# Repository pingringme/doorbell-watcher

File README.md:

# PingRing.me - Smart Doorbell

## 🌟 About PingRing.me

PingRing.me modernizes your existing doorbell by adding notifications via SMS, WhatsApp, HTTP, MQTT, and more. This enhancement ensures you never miss a visitor, whether you're outside or wearing noise-canceling headphones. The system integrates seamlessly with your current doorbell setup, allowing you to track arrivals and receive timely notifications.

## 🛠️ Features

- **Multi-Channel Notifications:** Receive alerts through SMS, WhatsApp, HTTP, MQTT, etc.
- **Seamless Integration:** Compatible with existing doorbell systems.
- **Local Web Server:** Access device information and perform over-the-air updates.
- **Open Source:** Hardware designs and code are publicly available.

## 📸 Visuals

Check [website here https://pingring.me](https://pingring.me)

## 🛠️ Tech Stack

- **Microcontroller:** ESP32-PICO-D4
- **Programming Language:** C (Arduino)
- **Cloud Functions:** AWS Lambda (Python)
- **Hardware Platform:** [TinyPICO USB-C](https://www.tinypico.com)

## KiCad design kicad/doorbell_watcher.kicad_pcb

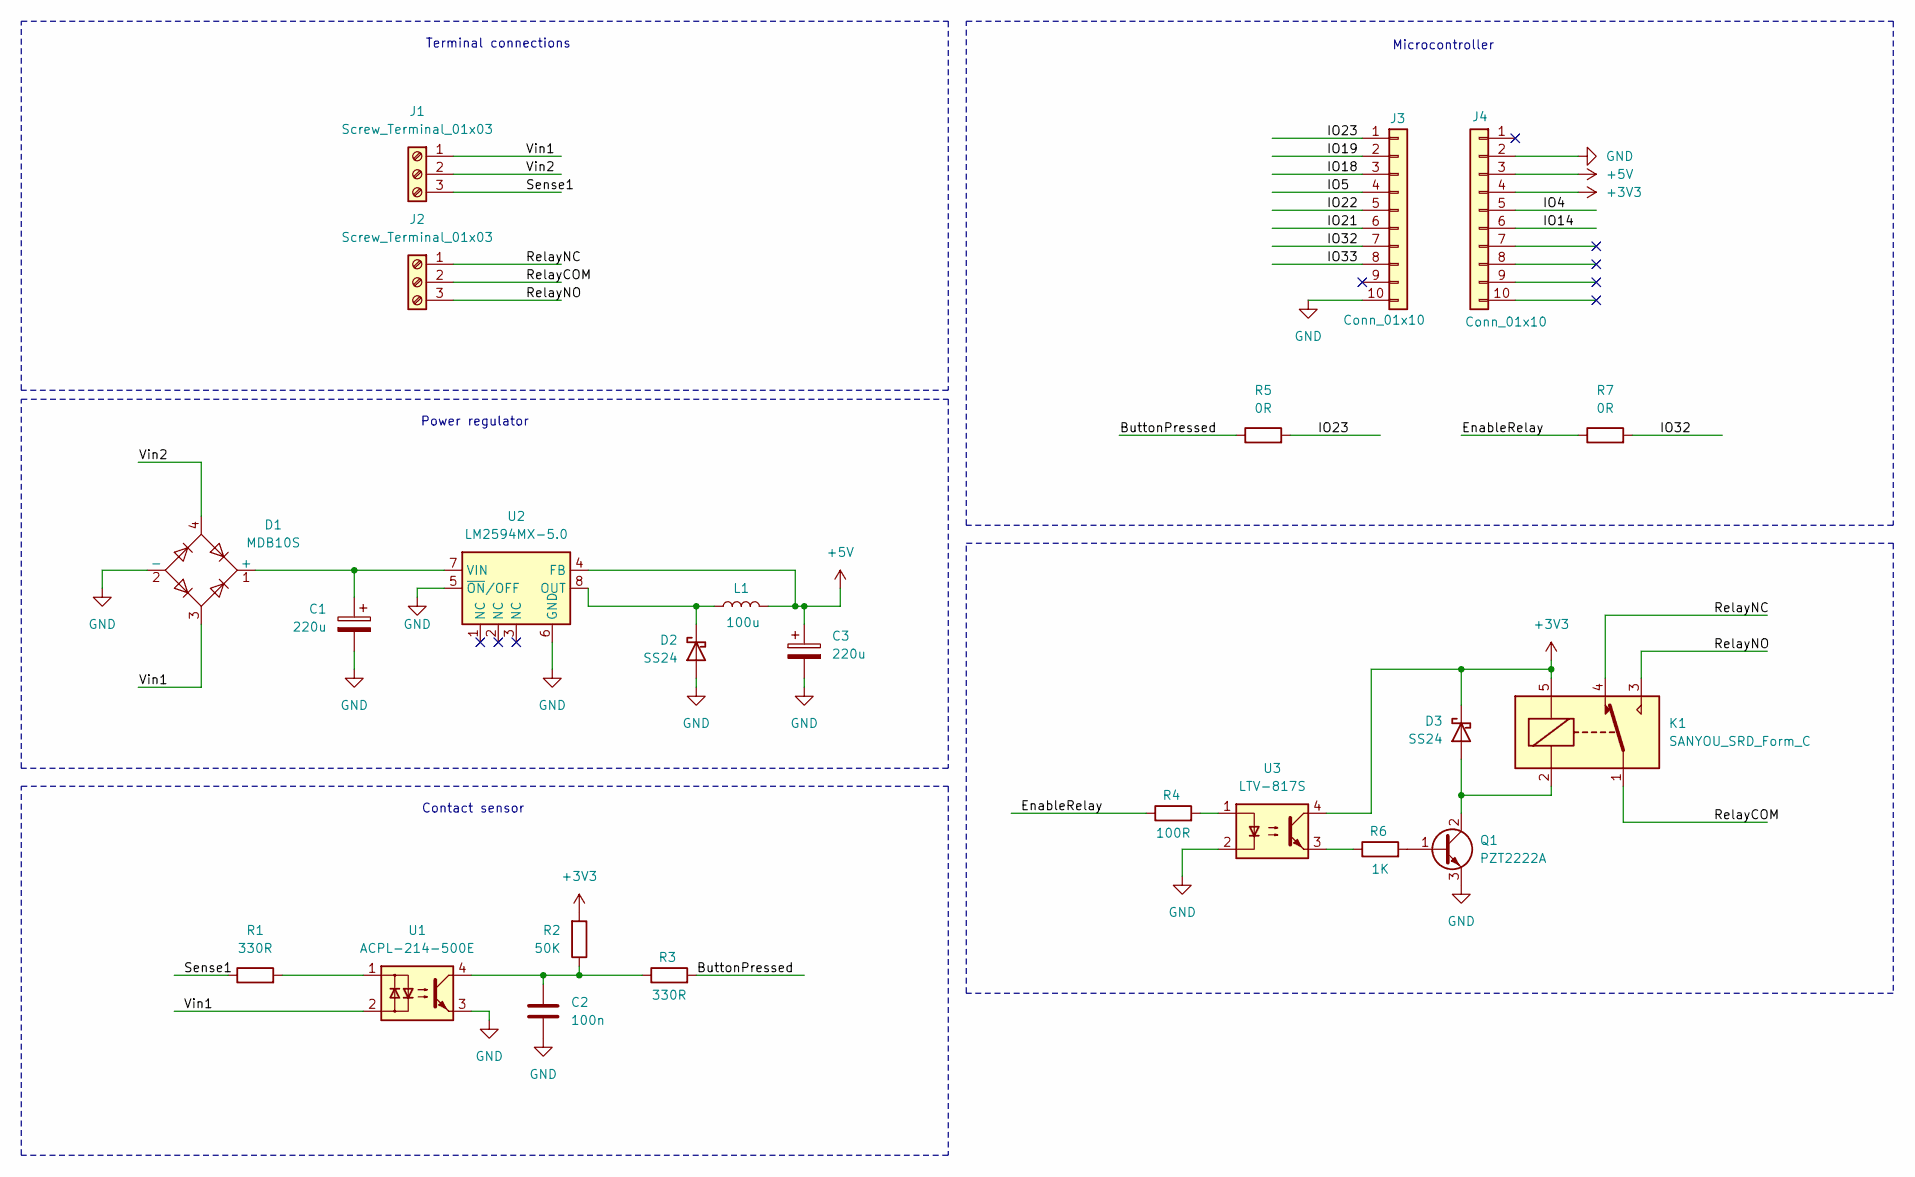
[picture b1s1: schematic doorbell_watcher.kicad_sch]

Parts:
C1, C3: 220u; CAP_FT_F_PAN-M; LCSC C178594
C2: 100n; C_0805_2012Metric_Pad1.18x1.45mm_HandSolder; LCSC C49678
D1: MDB10S; TSSOP4-MICRO-DIP_948BS_ONS-M; LCSC C258169
D2, D3: SS24; DO-214AC(SMA); LCSC C211773
J1, J2: Screw_Terminal_01x03; screw_connector_1x3; LCSC C589616
J3, J4: Conn_01x10; 10-pin header; LCSC C225507
K1: SANYOU_SRD_Form_C; Relay_SPDT_SANYOU_SRD_Series_Form_C; LCSC C24585
L1: 100u; IND_829SNLT_PUL; LCSC C2453068
Q1: PZT2222A; SOT-223-3_TabPin2; LCSC C115272
R1, R3: 330R; R_0805_2012Metric_Pad1.20x1.40mm_HandSolder; LCSC C17630
R2: 50K; R_0805_2012Metric_Pad1.20x1.40mm_HandSolder; LCSC C2828840
R4: 100R; R_0805_2012Metric_Pad1.20x1.40mm_HandSolder; LCSC C17408
R5, R7: 0R; R_0805_2012Metric_Pad1.20x1.40mm_HandSolder; LCSC C17477
R6: 1K; R_0805_2012Metric_Pad1.20x1.40mm_HandSolder; LCSC C95781
U1: ACPL-214-500E; SOP-4_4.4x2.6mm_P1.27mm; LCSC C5361360
U2: LM2594MX-5.0; SOIC-8_3.9x4.9mm_P1.27mm; LCSC C35323
U3: LTV-817S; SMDIP-4_W9.53mm; LCSC C125121

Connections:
+3V3: D3.1 (K), J4.4, K1.5, R2.2, U3.4
+5V: C3.1, J4.3, L1.2, U2.4 (FB)
/ButtonPressed: R3.2, R5.1
/EnableRelay: R4.1, R7.1
/IO4: J4.5
/IO5: J3.4
/IO14: J4.6
/IO18: J3.3
/IO19: J3.2
/IO21: J3.6
/IO22: J3.5
/IO23: J3.1, R5.2
/IO32: J3.7, R7.2
/IO33: J3.8
/RelayCOM: J2.2, K1.1
/RelayNC: J2.1, K1.4
/RelayNO: J2.3, K1.3
/Sense1: J1.3, R1.1
/Vin1: D1.3, J1.1, U1.2
/Vin2: D1.4, J1.2
GND: C1.2, C2.2, C3.2, D1.2 (-), D2.2 (A), J3.10, J4.2, Q1.3 (E), U1.3, U2.5 (~ON/OFF), U2.6 (GND), U3.2
unnamed: C2.1, R2.1, R3.1, U1.4
unnamed: C1.1, D1.1 (+), U2.7 (VIN)
unnamed: D2.1 (K), L1.1, U2.8 (OUT)
unnamed: D3.2 (A), K1.2, Q1.2 (C)
unnamed: Q1.1 (B), R6.2
unnamed: R1.2, U1.1
unnamed: R4.2, U3.1
unnamed: R6.1, U3.3

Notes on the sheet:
Contact sensor
Terminal connections
Microcontroller
Power regulator

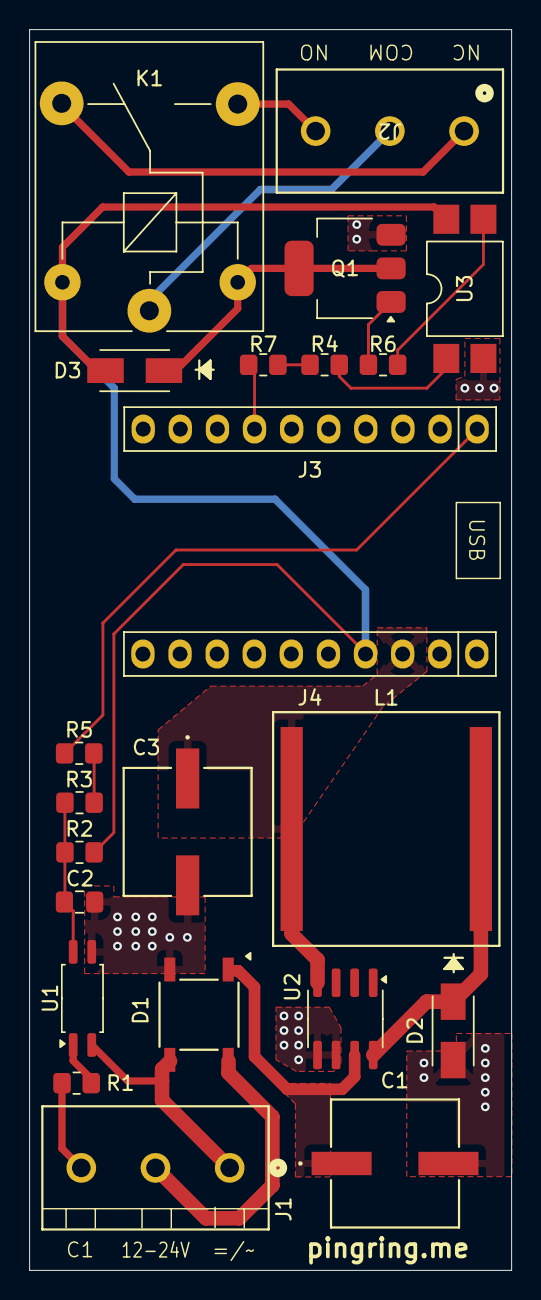
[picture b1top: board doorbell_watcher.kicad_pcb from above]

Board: 2 copper layers, 33.0 x 84.9 mm, 23 parts (0 on the bottom side), 21 nets.

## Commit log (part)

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2024-11-24 Add power stage simulation and first schematic draft.
2024-11-24 Added button signal simulation. Schematic is complete.
2024-11-24 Removed autogenerated files from LTSpice
2024-11-24 Change datasheet to datasheets
2024-11-25 Placement done
2024-11-26 Routing complete, changed LM2596 to LM2594
2024-11-26 Added fabrication files
2024-11-27 First fabrication release done
2024-11-29 Fix MDB9S footprint
2024-12-11 Fix unconnected 5V pin in ESP32 header
2024-12-12 Adding my arduino sketch code
2024-12-16 Add relay
2025-01-09 fixing potential wifi reconnecting issues, adding OTA, bell counter and NTP time.
2025-01-11 Storing start-up time
2025-01-11 Adding more stats...
2025-07-16 feat: adding silent mode
2025-07-19 fix: avoid sleeping the device after bell :)
2025-08-06 feat: silence http request when pressed too often
2025-11-25 Implement MQTT+HA support and update firmware version
    Added MQTT configuration and functionality to the doorbell system, including state and discovery topics. Updated firmware version and added mDNS support.
2025-11-26 feat: enhance HTML template, implementing Bootstrap5
    improved HTML template for device status :)
2026-03-25 Update lambda_function.py
    Adding different sources/UUID
2026-05-17 feat: Extract configuration to config.h
    Add a new arduino/config.h and move all configuration constants out of main.ino. The header introduces header guards and contains firmware/version, timing values, HTTP/WiFi/MQTT settings, NTP, pins, 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
2026-05-17 Improve MQTT/HTTP, add debounce & UI fixes
    Multiple improvements and fixes across Arduino firmware:
    - Added DEBOUNCE_MS and implemented pollBellButton() for software debouncing of the bell GPIO.
    - Wait for NTP sync at boot (with timeout) before stamping startup time.
    - Enhance MQTT handling: add mDNS broker resolution, rate-limited non-blocking reconnects (ensureMqttConnected), last-reconnect tracking, and separated publishMqttDiscovery() to send Home Assistant d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
    - Fix JSON HTTP responses (send valid JSON strings) and add Cache-Control: no-store on status page. Add RSSI units to the UI.
    - Use WiFiClientSecure for outbound HTTPS requests,
2026-05-17 Track relay activations and extend duration
    Increase relay pulse from 500ms to 750ms and add runtime observability for relay usage. Introduces relayActivations counter and lastRelayDateTime string (initialized to "never"); increments the count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
2026-05-17 fix: Bump firmware; adjust timings, UI and IO
    Bump FIRMWARE_VERSION and shorten various sleep intervals for faster responsiveness (setup, relay-after-bell and HTTP-after-bell). Remove URL scheme from HTTP_SERVER_URL placeholder. Update web UI he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
2026-05-17 fix: Use fixed buffers for datetimes & tweak bell logic
    Bump firmware version and refactor datetime handling to use fixed-size char buffers (no heap allocations) via fillDateTimeString(). Replace String-based timestamps with startupDateTime and lastRelayD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
2026-05-19 feat: Mirror-mode relay control and max-on safety
    Introduce mirror-mode relay state and safety cap to avoid GPIO contention and stuck relay situations. Added RELAY_MAX_ON_MS to config.h. In main.ino, add relayOn/relayOnSince state and non-blocking r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
    Tigh
2026-05-19 feat: Bump firmware version; reduce monitoring interval
    Update arduino/config.h: bump FIRMWARE_VERSION timestamp and lower MONITORING_INTERVAL_MS from 100 to 25 ms. The shorter monitoring interval ensures at least two samples per DEBOUNCE_MS window and im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
2026-05-19 feat: Add Telegram + AWS notifications, refactor HTTP
    Bump firmware version and introduce pluggable notification backends (NOTIFY_AWS_ENABLED, NOTIFY_TELEGRAM_ENABLED) and Telegram config (TELEGRAM_BOT_TOKEN, TELEGRAM_CHAT_ID) in config.h. Factor out a 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
2026-05-19 fix: HTTPClient::urlEncode is not available in arduino :( Use local urlEncode for Telegram; bump firmware
    Add a local RFC3986-compliant urlEncode(String) helper and use it to percent-encode Telegram message text (avoids '+' for spaces and works around arduino-esp32 HTTPClient not exposing urlEncode). Als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
2026-05-19 fix: Use runtime notify flags; expand config docs
    Replace compile-time NOTIFY_AWS/TELEGRAM macros with runtime booleans (notify_aws_enabled, notify_telegram_enabled). Update dispatchNotifications to check those runtime flags instead of #if guards, a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
